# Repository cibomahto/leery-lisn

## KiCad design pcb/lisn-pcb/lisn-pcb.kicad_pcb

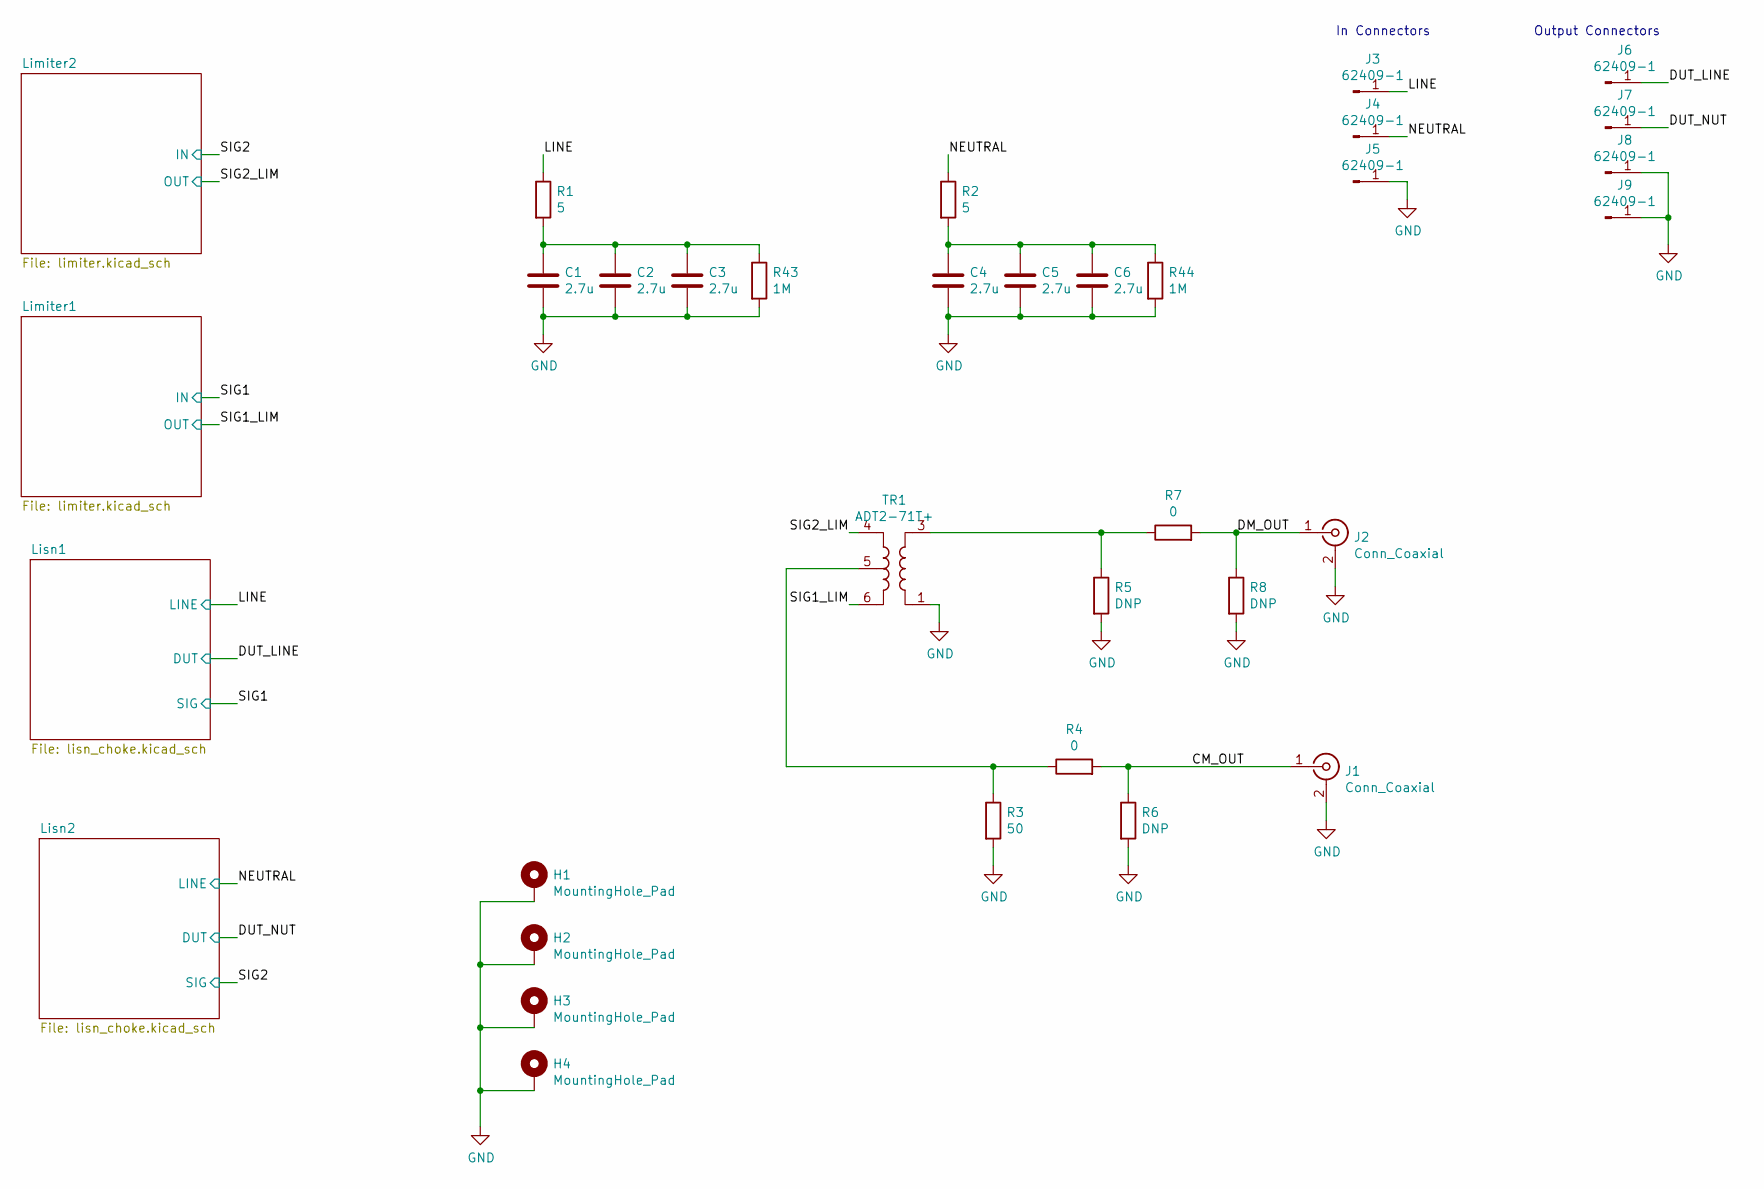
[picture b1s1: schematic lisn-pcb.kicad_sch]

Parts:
C1, C2, C3, C4, C5, C6: 2.7u; C_Rect_L31.5mm_W20.0mm_P27.50mm_MKS4; MPN ECQ-UAAF275K
H1, H2, H3, H4: MountingHole_Pad; M3-tight-fit-socket-head
J1, J2: Conn_Coaxial; SMA_Amphenol_132203-12_Horizontal; MPN 619540-1
J3, J4, J5, J6, J7, J8, J9: 62409-1; MPN 62409-1
R1, R2: 5; R_Axial_Power_L20.0mm_W6.4mm_P25.40mm; MPN WNE5R0FET
R3: 50; R_0805_2012Metric; MPN RNCP0805FTD49R9
R4, R7: 0; R_0805_2012Metric; MPN RC0805JR-070RL
R5, R6, R8: DNP; R_0805_2012Metric
R43, R44: 1M; R_Axial_DIN0414_L11.9mm_D4.5mm_P15.24mm_Horizontal; MPN ROX1SJ1M0
TR1: ADT2-71T+; Mini-Circuits_CD637_H5.23mm; MPN ADT2-71T+

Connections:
/CM_OUT: J1.1 (In), R4.2, R6.1
/DM_OUT: J2.1 (In), R7.2, R8.1
/DUT_LINE: J6.1; also elsewhere on the board
/DUT_NUT: J7.1; also elsewhere on the board
/LINE: J3.1, R1.1; also elsewhere on the board
/NEUTRAL: J4.1, R2.1; also elsewhere on the board
/SIG1_LIM: TR1.6; also elsewhere on the board
/SIG2_LIM: TR1.4; also elsewhere on the board
GND: C1.2, C2.2, C3.2, C4.2, C5.2, C6.2, H1.1, H2.1, H3.1, H4.1, J1.2 (Ext), J2.2 (Ext), J5.1, J8.1, J9.1, R3.2, R5.2, R6.2, R8.2, R43.2, R44.2, TR1.1; also elsewhere on the board
unnamed: C1.1, C2.1, C3.1, R1.2, R43.1
unnamed: C4.1, C5.1, C6.1, R2.2, R44.1
unnamed: R3.1, R4.1, TR1.5
unnamed: R5.1, R7.1, TR1.3

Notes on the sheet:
Output Connectors
In Connectors

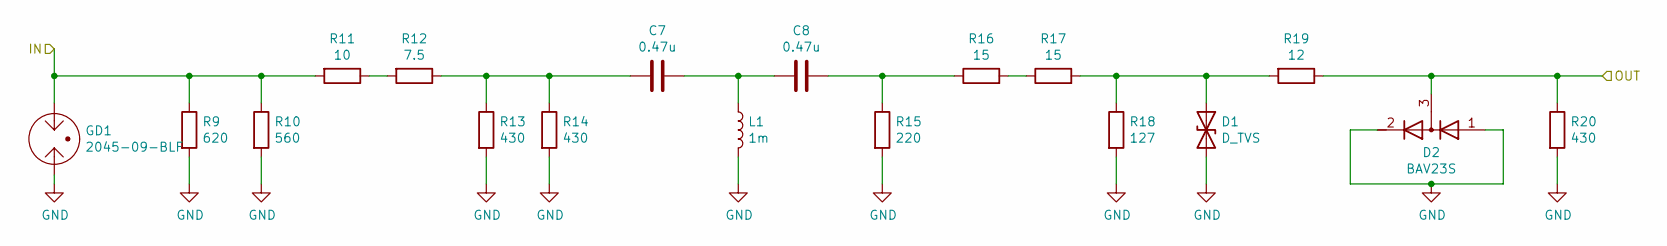
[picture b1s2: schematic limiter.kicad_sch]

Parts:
C7, C8: 0.47u; C_0805_2012Metric; MPN 08051C474K4Z2A
D1: D_TVS; D_SOD-323; MPN STS321050B100
D2: BAV23S; SOT-23; MPN BAV23S,215
GD1: 2045-09-BLF; GDT_Bourns_2045; MPN 2045-09-BLF
L1: 1m; L_BOURNS_PM1812; MPN PM1812-102J-RC
R9: 620; R_0805_2012Metric; MPN RCS0805620RFKEA
R10: 560; R_0805_2012Metric; MPN RCS0805560RFKEA
R11: 10; R_0805_2012Metric; MPN RCS080510R0FKEA
R12: 7.5; R_0805_2012Metric; MPN RCS08057R50FKEA
R13, R14, R20: 430; R_0805_2012Metric; MPN ESR10EZPF4300
R15: 220; R_0805_2012Metric; MPN RCS0805220RFKEA
R16, R17: 15; R_0805_2012Metric; MPN RCS080515R0FKEA
R18: 127; R_0805_2012Metric; MPN RK73H2ATTD1270F
R19: 12; R_0805_2012Metric; MPN ERJ-6ENF12R0V

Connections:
/SIG1: GD1.1, R9.1, R10.1, R11.2; also elsewhere on the board
/SIG1_LIM: D2.3 (common), R19.1, R20.1; also elsewhere on the board
GND: D1.2 (A2), D2.1 (A), D2.2 (K), GD1.2, L1.2, R9.2, R10.2, R13.2, R14.2, R15.2, R18.2, R20.2; also elsewhere on the board
unnamed: C7.1, C8.2, L1.1
unnamed: C7.2, R12.1, R13.1, R14.1
unnamed: C8.1, R15.1, R16.1
unnamed: D1.1 (A1), R17.2, R18.1, R19.2
unnamed: R11.1, R12.2
unnamed: R16.2, R17.1

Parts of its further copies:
C10, C11: 0.47u; C_0805_2012Metric; MPN 08051C474K4Z2A
D3: D_TVS; D_SOD-323; MPN STS321050B100
D4: BAV23S; SOT-23; MPN BAV23S,215
GD2: 2045-09-BLF; GDT_Bourns_2045; MPN 2045-09-BLF
L7: 1m; L_BOURNS_PM1812; MPN PM1812-102J-RC
R26: 620; R_0805_2012Metric; MPN RCS0805620RFKEA
R27: 560; R_0805_2012Metric; MPN RCS0805560RFKEA
R28: 10; R_0805_2012Metric; MPN RCS080510R0FKEA
R29: 7.5; R_0805_2012Metric; MPN RCS08057R50FKEA
R30, R31, R37: 430; R_0805_2012Metric; MPN ESR10EZPF4300
R32: 220; R_0805_2012Metric; MPN RCS0805220RFKEA
R33, R34: 15; R_0805_2012Metric; MPN RCS080515R0FKEA
R35: 127; R_0805_2012Metric; MPN RK73H2ATTD1270F
R36: 12; R_0805_2012Metric; MPN ERJ-6ENF12R0V

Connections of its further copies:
/SIG2: GD2.1, R26.1, R27.1, R28.2; also elsewhere on the board
/SIG2_LIM: D4.3 (common), R36.1, R37.1; also elsewhere on the board
GND: D3.2 (A2), D4.1 (A), D4.2 (K), GD2.2, L7.2, R26.2, R27.2, R30.2, R31.2, R32.2, R35.2, R37.2; also elsewhere on the board
unnamed: C10.1, C11.2, L7.1
unnamed: C10.2, R29.1, R30.1, R31.1
unnamed: C11.1, R32.1, R33.1
unnamed: D3.1 (A1), R34.2, R35.1, R36.2
unnamed: R28.1, R29.2
unnamed: R33.2, R34.1

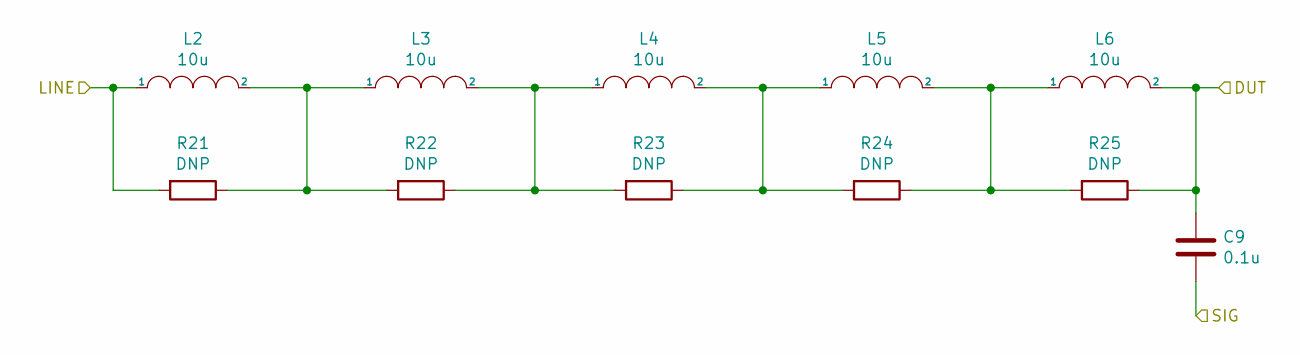
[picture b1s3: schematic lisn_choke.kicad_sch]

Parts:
C9: 0.1u; C_Rect_L26.5mm_W10.5mm_P22.50mm_MKS4; MPN BFC233860104
L2, L3, L4, L5, L6: 10u; L_WURTH_WE-HCC-1090; MPN 7443331000
R21, R22, R23, R24, R25: DNP; R_1206_3216Metric

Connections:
/DUT_LINE: C9.1, L6.2, R25.1; also elsewhere on the board
/LINE: L2.1, R21.2; also elsewhere on the board
/SIG1: C9.2; also elsewhere on the board
unnamed: L2.2, L3.1, R21.1, R22.2
unnamed: L3.2, L4.1, R22.1, R23.2
unnamed: L4.2, L5.1, R23.1, R24.2
unnamed: L5.2, L6.1, R24.1, R25.2

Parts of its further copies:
C12: 0.1u; C_Rect_L26.5mm_W10.5mm_P22.50mm_MKS4; MPN BFC233860104
L8, L9, L10, L11, L12: 10u; L_WURTH_WE-HCC-1090; MPN 7443331000
R38, R39, R40, R41, R42: DNP; R_1206_3216Metric

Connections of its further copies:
/DUT_NUT: C12.1, L12.2, R42.1; also elsewhere on the board
/NEUTRAL: L8.1, R38.2; also elsewhere on the board
/SIG2: C12.2; also elsewhere on the board
unnamed: L8.2, L9.1, R38.1, R39.2
unnamed: L9.2, L10.1, R39.1, R40.2
unnamed: L10.2, L11.1, R40.1, R41.2
unnamed: L11.2, L12.1, R41.1, R42.2

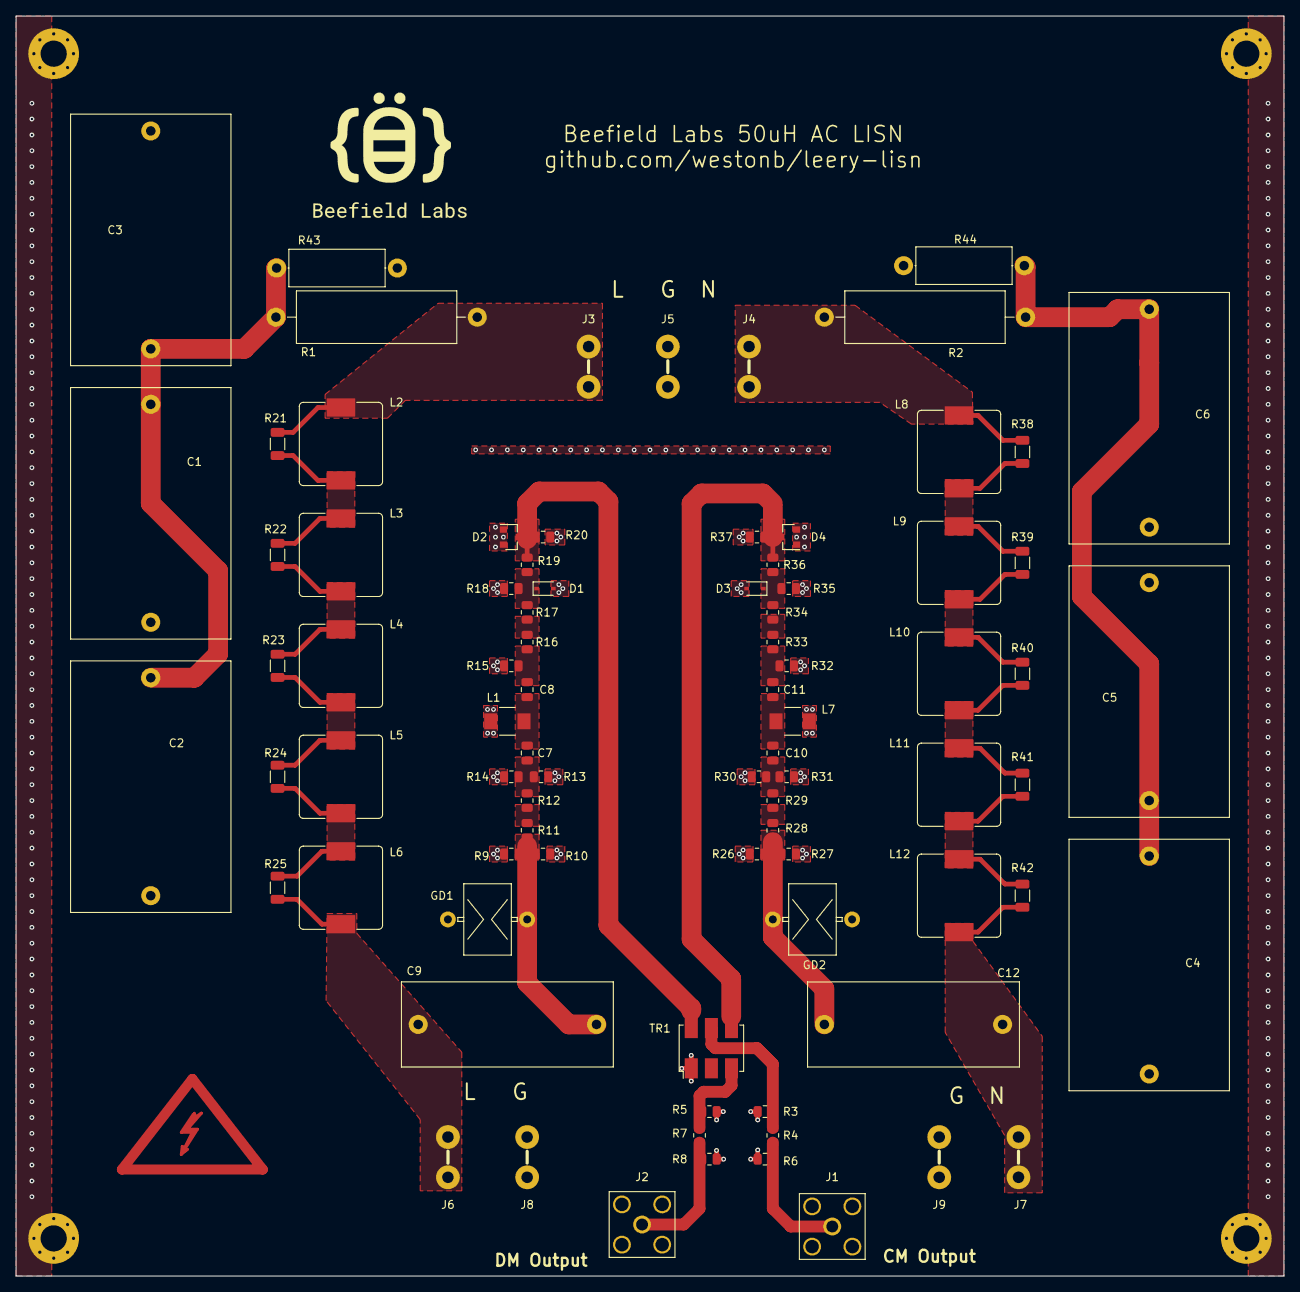
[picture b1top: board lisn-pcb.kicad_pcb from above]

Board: 2 copper layers, 160.0 x 159.0 mm, 88 parts (0 on the bottom side), 35 nets.

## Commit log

2024-12-04 Bump to KiCad 8, add BOM info
2024-12-10 Add bleed resistors
2024-12-20 Use a larger value for the bleed resistors
2024-12-20 Ignore temporary files
